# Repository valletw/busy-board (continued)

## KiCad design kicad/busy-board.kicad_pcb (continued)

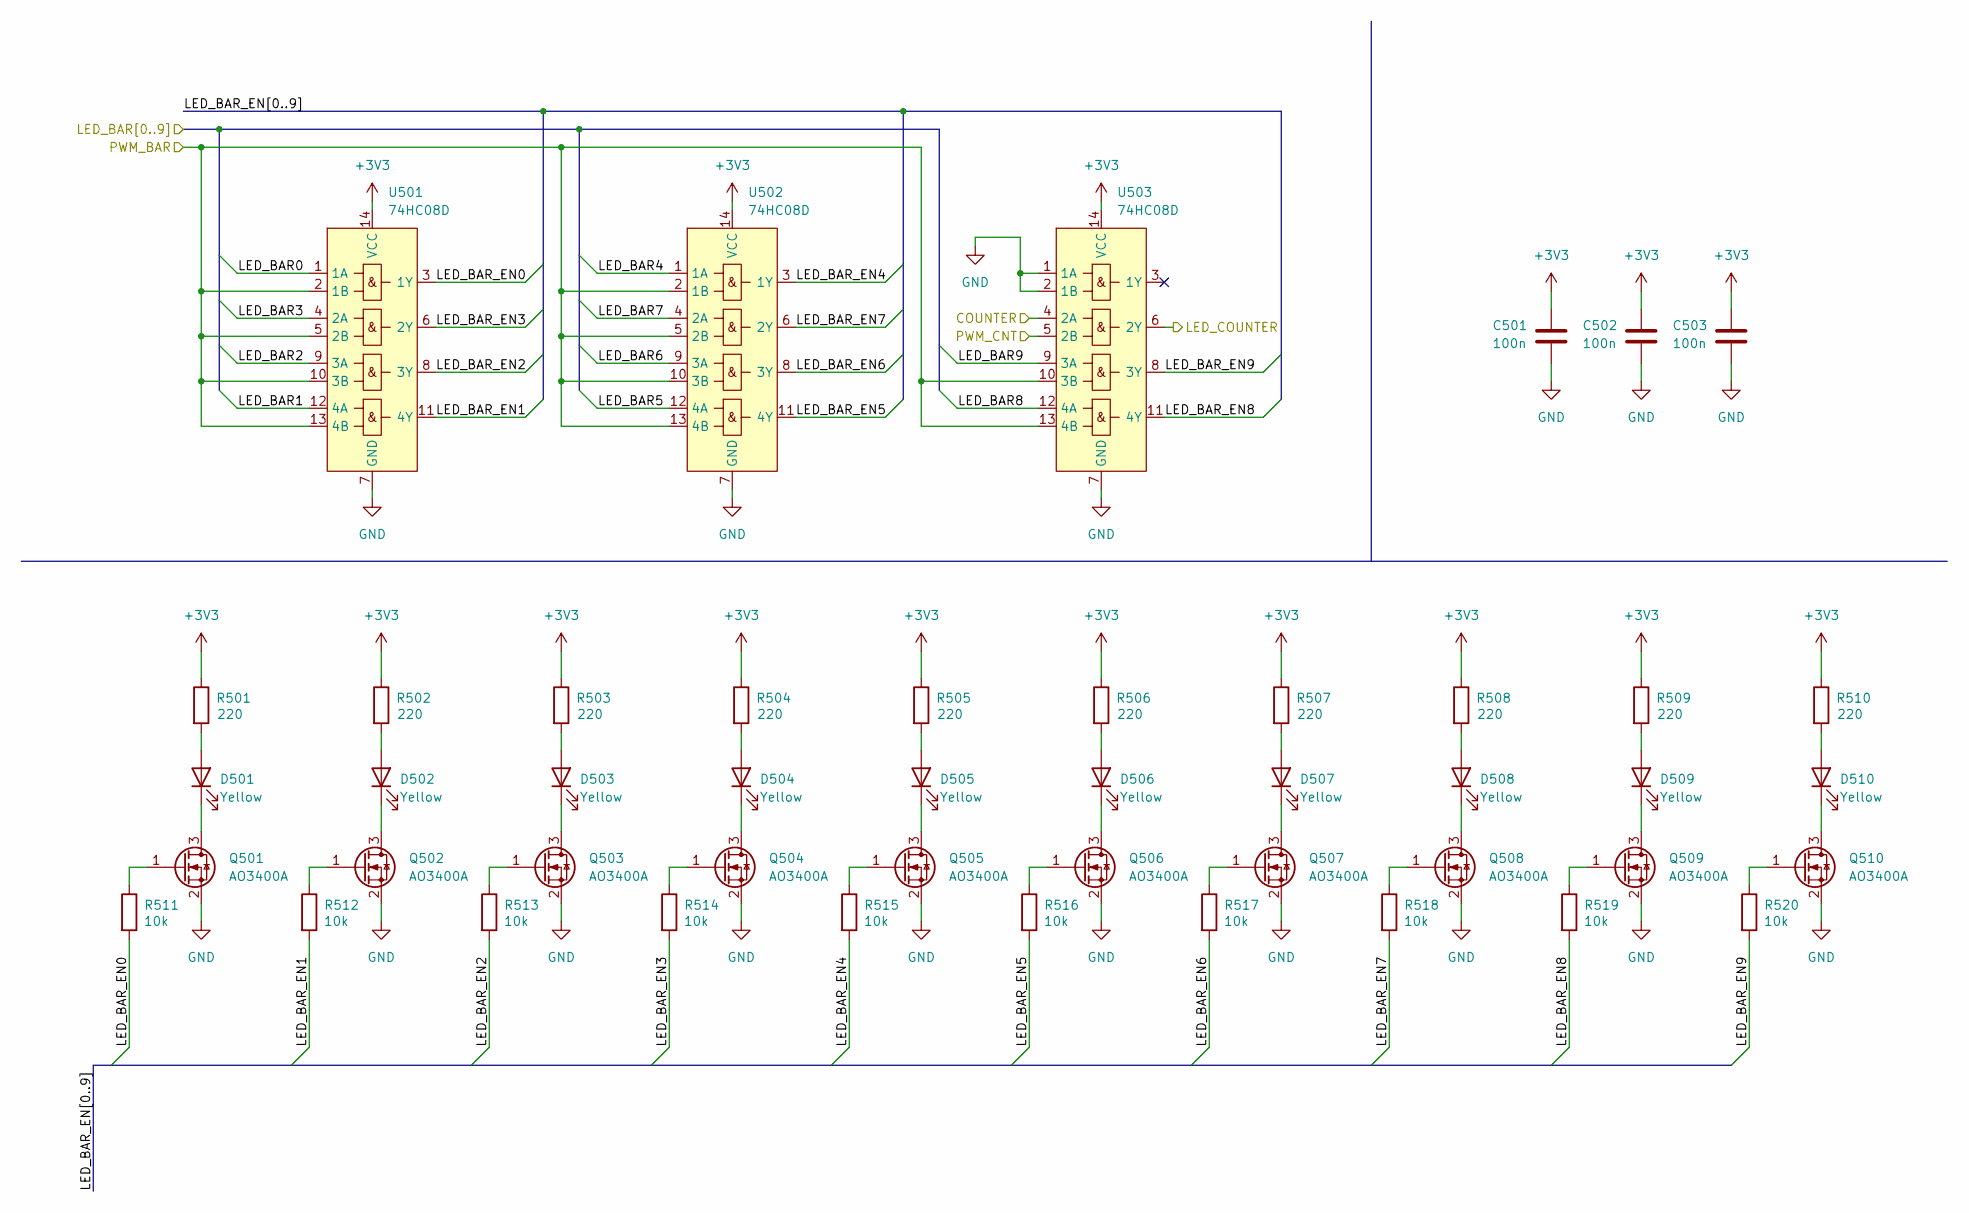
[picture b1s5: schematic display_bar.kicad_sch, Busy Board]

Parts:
C501, C502, C503: 100n; C_0402_1005Metric; MFR Part # CL05B104KB54PNC; LCSC Part # C307331
D501, D502, D503, D504, D505, D506, D507, D508, D509, D510: Yellow; LED_0805_2012Metric; MFR Part # KT-0805Y; LCSC Part # C2296
Q501, Q502, Q503, Q504, Q505, Q506, Q507, Q508, Q509, Q510: AO3400A; SOT-23; MFR Part # AO3400A; LCSC Part # C20917
R501, R502, R503, R504, R505, R506, R507, R508, R509, R510: 220; R_0603_1608Metric; MFR Part # 0603WAF2200T5E; LCSC Part # C22962
R511, R512, R513, R514, R515, R516, R517, R518, R519, R520: 10k; R_0603_1608Metric; MFR Part # 0603WAF1002T5E; LCSC Part # C25804
U501, U502, U503: 74HC08D; SOIC-14_3.9x8.7mm_P1.27mm; MFR Part # 74HC08D,653; LCSC Part # C5593

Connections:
+3V3: C501.1, C502.1, C503.1, R501.1, R502.1, R503.1, R504.1, R505.1, R506.1, R507.1, R508.1, R509.1, R510.1, U501.14 (VCC), U502.14 (VCC), U503.14 (VCC); also elsewhere on the board
/CLK_CNT: U503.4 (2A); also elsewhere on the board
/Counter/Display Bar/LED_BAR_EN0: R511.2, U501.3 (1Y)
/Counter/Display Bar/LED_BAR_EN1: R512.2, U501.11 (4Y)
/Counter/Display Bar/LED_BAR_EN2: R513.2, U501.8 (3Y)
/Counter/Display Bar/LED_BAR_EN3: R514.2, U501.6 (2Y)
/Counter/Display Bar/LED_BAR_EN4: R515.2, U502.3 (1Y)
/Counter/Display Bar/LED_BAR_EN5: R516.2, U502.11 (4Y)
/Counter/Display Bar/LED_BAR_EN6: R517.2, U502.8 (3Y)
/Counter/Display Bar/LED_BAR_EN7: R518.2, U502.6 (2Y)
/Counter/Display Bar/LED_BAR_EN8: R519.2, U503.11 (4Y)
/Counter/Display Bar/LED_BAR_EN9: R520.2, U503.8 (3Y)
/Counter/LED_BAR0: U501.1 (1A); also elsewhere on the board
/Counter/LED_BAR1: U501.12 (4A); also elsewhere on the board
/Counter/LED_BAR2: U501.9 (3A); also elsewhere on the board
/Counter/LED_BAR3: U501.4 (2A); also elsewhere on the board
/Counter/LED_BAR4: U502.1 (1A); also elsewhere on the board
/Counter/LED_BAR5: U502.12 (4A); also elsewhere on the board
/Counter/LED_BAR6: U502.9 (3A); also elsewhere on the board
/Counter/LED_BAR7: U502.4 (2A); also elsewhere on the board
/Counter/LED_BAR8: U503.12 (4A); also elsewhere on the board
/Counter/LED_BAR9: U503.9 (3A); also elsewhere on the board
/Counter/LED_COUNTER: U503.6 (2Y); also elsewhere on the board
/Counter/PWM_LED_BAR: U501.2 (1B), U501.5 (2B), U501.10 (3B), U501.13 (4B), U502.2 (1B), U502.5 (2B), U502.10 (3B), U502.13 (4B), U503.10 (3B), U503.13 (4B); also elsewhere on the board
/Counter/PWM_LED_COUNTER: U503.5 (2B); also elsewhere on the board
GND: C501.2, C502.2, C503.2, Q501.2 (S), Q502.2 (S), Q503.2 (S), Q504.2 (S), Q505.2 (S), Q506.2 (S), Q507.2 (S), Q508.2 (S), Q509.2 (S), Q510.2 (S), U501.7 (GND), U502.7 (GND), U503.1 (1A), U503.2 (1B), U503.7 (GND); also elsewhere on the board
unnamed: D501.2 (A), R501.2
unnamed: D501.1 (K), Q501.3 (D)
unnamed: D502.2 (A), R502.2
unnamed: D502.1 (K), Q502.3 (D)
unnamed: D503.2 (A), R503.2
unnamed: D503.1 (K), Q503.3 (D)
unnamed: D504.2 (A), R504.2
unnamed: D504.1 (K), Q504.3 (D)
unnamed: D505.2 (A), R505.2
unnamed: D505.1 (K), Q505.3 (D)
unnamed: D506.2 (A), R506.2
unnamed: D506.1 (K), Q506.3 (D)
unnamed: D507.2 (A), R507.2
unnamed: D507.1 (K), Q507.3 (D)
unnamed: D508.2 (A), R508.2
unnamed: D508.1 (K), Q508.3 (D)
unnamed: D509.2 (A), R509.2
unnamed: D509.1 (K), Q509.3 (D)
unnamed: D510.2 (A), R510.2
unnamed: D510.1 (K), Q510.3 (D)
unnamed: Q501.1 (G), R511.1
unnamed: Q502.1 (G), R512.1
unnamed: Q503.1 (G), R513.1
unnamed: Q504.1 (G), R514.1
unnamed: Q505.1 (G), R515.1
unnamed: Q506.1 (G), R516.1
unnamed: Q507.1 (G), R517.1
unnamed: Q508.1 (G), R518.1
unnamed: Q509.1 (G), R519.1
unnamed: Q510.1 (G), R520.1

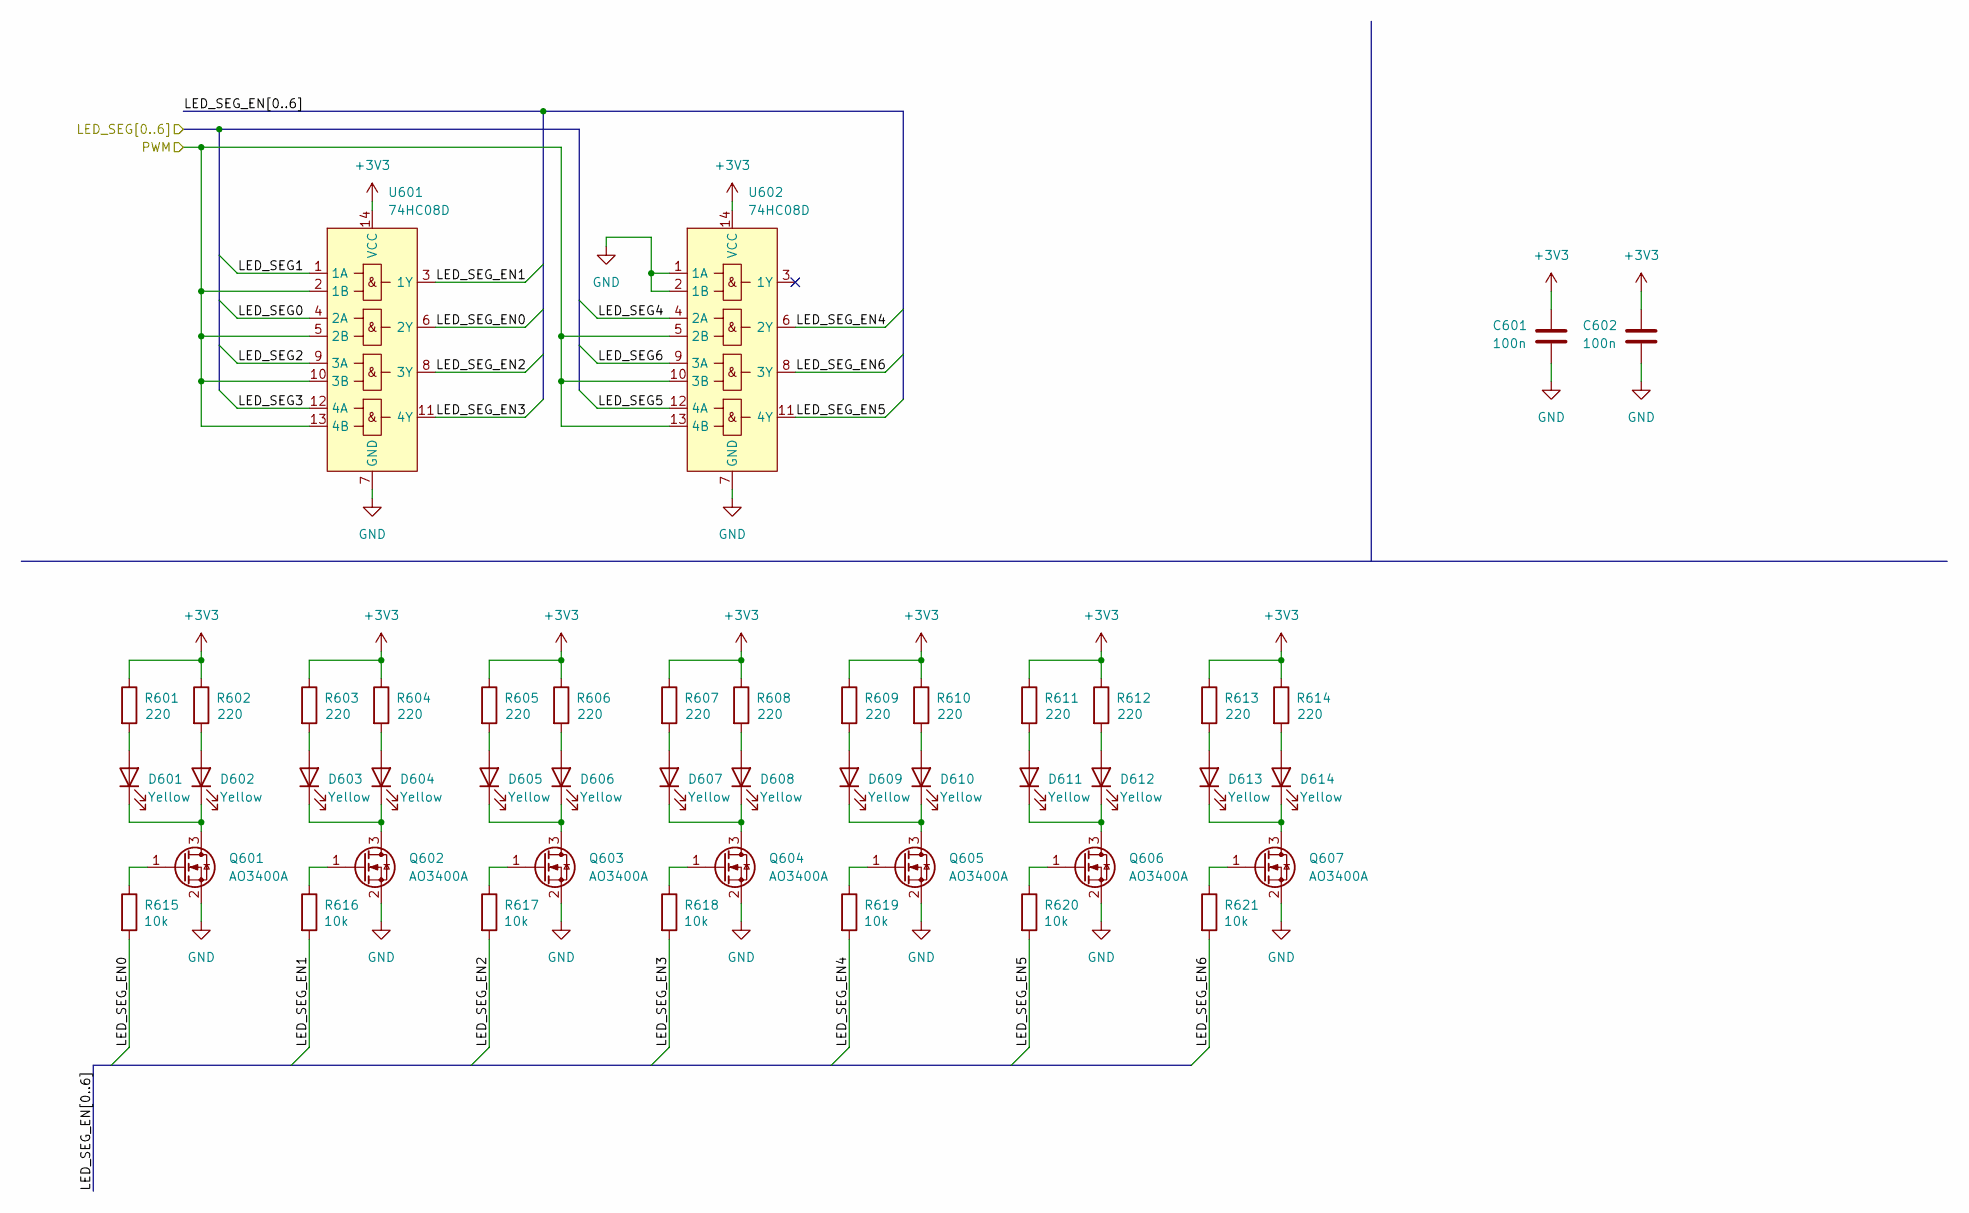
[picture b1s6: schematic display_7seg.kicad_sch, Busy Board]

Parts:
C601, C602: 100n; C_0402_1005Metric; MFR Part # CL05B104KB54PNC; LCSC Part # C307331
D601, D602, D603, D604, D605, D606, D607, D608, D609, D610, D611, D612, D613, D614: Yellow; LED_0805_2012Metric; MFR Part # KT-0805Y; LCSC Part # C2296
Q601, Q602, Q603, Q604, Q605, Q606, Q607: AO3400A; SOT-23; MFR Part # AO3400A; LCSC Part # C20917
R601, R602, R603, R604, R605, R606, R607, R608, R609, R610, R611, R612, R613, R614: 220; R_0603_1608Metric; MFR Part # 0603WAF2200T5E; LCSC Part # C22962
R615, R616, R617, R618, R619, R620, R621: 10k; R_0603_1608Metric; MFR Part # 0603WAF1002T5E; LCSC Part # C25804
U601, U602: 74HC08D; SOIC-14_3.9x8.7mm_P1.27mm; MFR Part # 74HC08D,653; LCSC Part # C5593

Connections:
+3V3: C601.1, C602.1, R601.1, R602.1, R603.1, R604.1, R605.1, R606.1, R607.1, R608.1, R609.1, R610.1, R611.1, R612.1, R613.1, R614.1, U601.14 (VCC), U602.14 (VCC); also elsewhere on the board
/Counter/Display 7 Segments/LED_SEG_EN0: R615.2, U601.6 (2Y)
/Counter/Display 7 Segments/LED_SEG_EN1: R616.2, U601.3 (1Y)
/Counter/Display 7 Segments/LED_SEG_EN2: R617.2, U601.8 (3Y)
/Counter/Display 7 Segments/LED_SEG_EN3: R618.2, U601.11 (4Y)
/Counter/Display 7 Segments/LED_SEG_EN4: R619.2, U602.6 (2Y)
/Counter/Display 7 Segments/LED_SEG_EN5: R620.2, U602.11 (4Y)
/Counter/Display 7 Segments/LED_SEG_EN6: R621.2, U602.8 (3Y)
/Counter/LED_SEG0: U601.4 (2A); also elsewhere on the board
/Counter/LED_SEG1: U601.1 (1A); also elsewhere on the board
/Counter/LED_SEG2: U601.9 (3A); also elsewhere on the board
/Counter/LED_SEG3: U601.12 (4A); also elsewhere on the board
/Counter/LED_SEG4: U602.4 (2A); also elsewhere on the board
/Counter/LED_SEG5: U602.12 (4A); also elsewhere on the board
/Counter/LED_SEG6: U602.9 (3A); also elsewhere on the board
/Counter/PWM_LED_SEG: U601.2 (1B), U601.5 (2B), U601.10 (3B), U601.13 (4B), U602.5 (2B), U602.10 (3B), U602.13 (4B); also elsewhere on the board
GND: C601.2, C602.2, Q601.2 (S), Q602.2 (S), Q603.2 (S), Q604.2 (S), Q605.2 (S), Q606.2 (S), Q607.2 (S), U601.7 (GND), U602.1 (1A), U602.2 (1B), U602.7 (GND); also elsewhere on the board
unnamed: D601.2 (A), R601.2
unnamed: D601.1 (K), D602.1 (K), Q601.3 (D)
unnamed: D602.2 (A), R602.2
unnamed: D603.2 (A), R603.2
unnamed: D603.1 (K), D604.1 (K), Q602.3 (D)
unnamed: D604.2 (A), R604.2
unnamed: D605.2 (A), R605.2
unnamed: D605.1 (K), D606.1 (K), Q603.3 (D)
unnamed: D606.2 (A), R606.2
unnamed: D607.2 (A), R607.2
unnamed: D607.1 (K), D608.1 (K), Q604.3 (D)
unnamed: D608.2 (A), R608.2
unnamed: D609.2 (A), R609.2
unnamed: D609.1 (K), D610.1 (K), Q605.3 (D)
unnamed: D610.2 (A), R610.2
unnamed: D611.2 (A), R611.2
unnamed: D611.1 (K), D612.1 (K), Q606.3 (D)
unnamed: D612.2 (A), R612.2
unnamed: D613.2 (A), R613.2
unnamed: D613.1 (K), D614.1 (K), Q607.3 (D)
unnamed: D614.2 (A), R614.2
unnamed: Q601.1 (G), R615.1
unnamed: Q602.1 (G), R616.1
unnamed: Q603.1 (G), R617.1
unnamed: Q604.1 (G), R618.1
unnamed: Q605.1 (G), R619.1
unnamed: Q606.1 (G), R620.1
unnamed: Q607.1 (G), R621.1

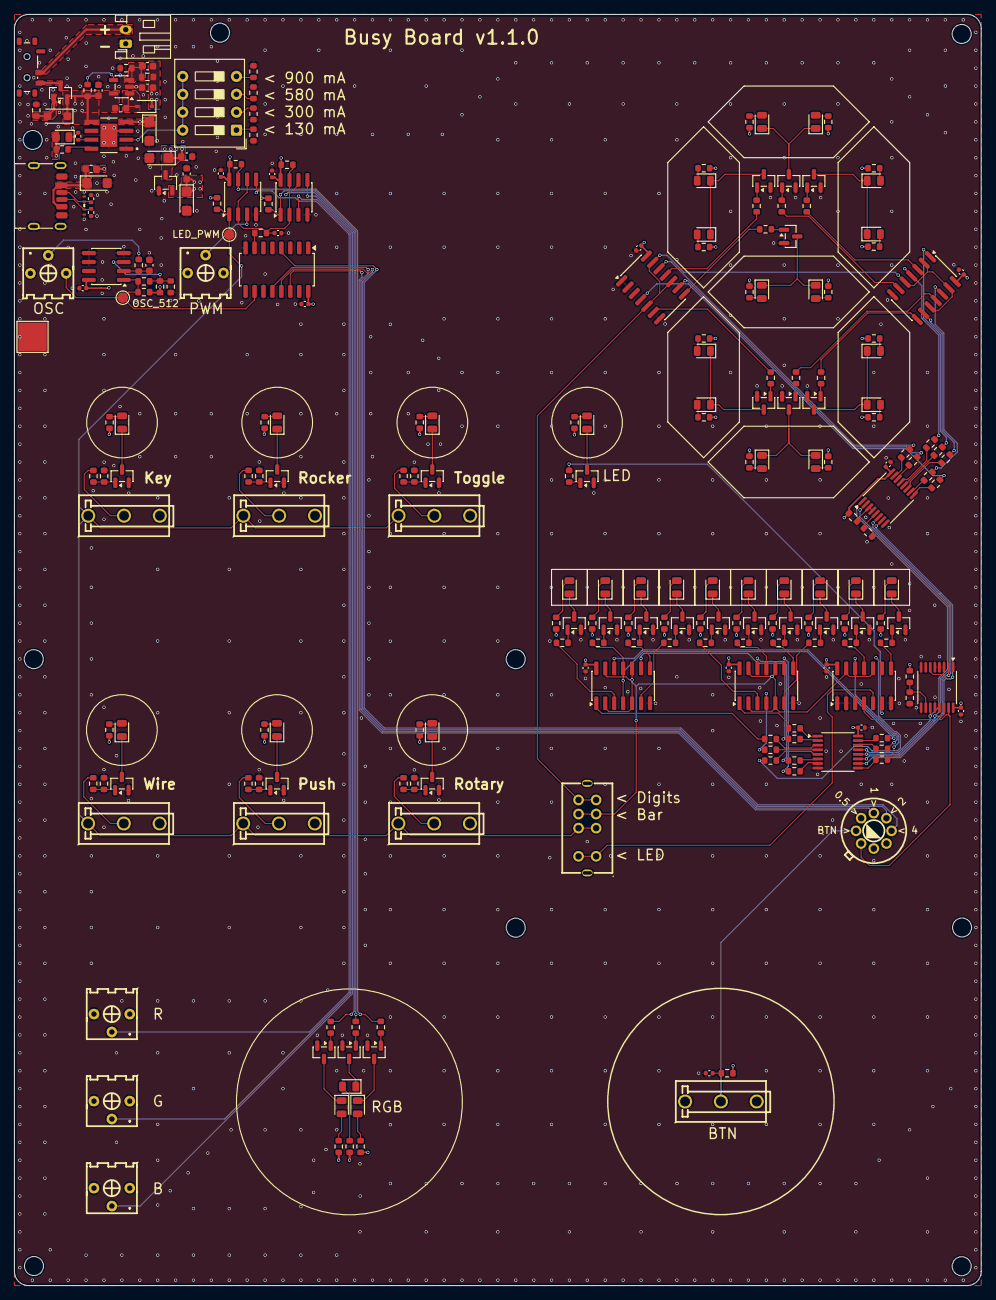
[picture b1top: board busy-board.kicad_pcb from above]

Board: 4 copper layers, 137.2 x 180.3 mm, 249 parts (0 on the bottom side), 198 nets.

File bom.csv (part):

"Reference","Value","Qty","Footprint","Manufacturer","MFR Part #","LCSC Part #","Datasheet"
"C101,C202,C204","100n","3","Capacitor_SMD:C_0603_1608Metric","YAGEO","CC0603JRX7R7BB104,CC0603KRX7R9BB104","C14663,C91183","https://jlcpcb.com/api/file/downloadByFileSystemAccessId/866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,https://www.lcsc.com/datasheet/C91183.pdf"
"C102,C103,C104,C105,C106,C107,C401,C402,C403,C501,C502,C503,C601,C602","100n","14","Capacitor_SMD:C_0402_1005Metric","Samsung Electro-Mechanics","CL05B104KB54PNC","C307331","https://jlcpcb.com/api/file/downloadByFileSystemAccessId/855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"
"C201,C203,C208","10u","3","Capacitor_Tantalum_SMD:CP_EIA-3216-18_Kemet-A","-","TAJA106K016RNJ","C7171","~"
"C205","22p","1","Capacitor_SMD:C_0603_1608Metric","Samsung Electro-Mechanics","CL10C220JB8NNNC","C1653","https://jlcpcb.com/api/file/downloadByFileSystemAccessId/866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"
"C206","1u","1","Capacitor_SMD:C_0603_1608Metric","Samsung Electro-Mechanics","CL10A105KB8NNNC","C15849","https://jlcpcb.com/api/file/downloadByFileSystemAccessId/866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"
"C207","4.7u","1","Capacitor_SMD:C_0603_1608Metric","Samsung Electro-Mechanics","CL10A475KO8NNNC","C19666","https://jlcpcb.com/api/file/downloadByFileSystemAccessId/866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 0 0 Centrer Centrer 0 0"
"D201","BZT52Bxx","1","Diode_SMD:D_SOD-123F","hongjiacheng","BZT52B5V1","C19077393","https://diotec.com/tl_files/diotec/files/pdf/datasheets/bzt5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"
"D202","SMF5V0A","1","Diode_SMD:D_SMF","hongjiacheng","SMF5.0A","C19077497","https://www.vishay.com/doc?85881"
"D203","B0540WS","1","Diode_SMD:D_SOD-323","hongjiacheng","B0540WS","C7420326","https://jlc-prod-smt.oss-eu-central-1.aliyuncs.com/smtDataMa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"
"D204,D301,D304","Red","3","LED_SMD:LED_0805_2012Metric","Foshan NationStar Optoelectronics","NCD0805R1","C84256","https://jlcpcb.com/api/file/downloadByFileSystemAccessId/855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,https://www.lcsc.com/datasheet/C84256.pdf"
"D302,D306","Green","2","LED_SMD:LED_0805_2012Metric","Hubei KENTO Elec","KT-0805G","C2297","https://www.lcsc.com/datasheet/C2297.pdf"
"D303,D308","Blue","2","LED_SMD:LED_0805_2012Metric","Foshan NationStar Optoelectronics","NCD0805B2","C84259","https://www.lcsc.com/datasheet/C84259.pdf"
"D305","Orange","1","LED_SMD:LED_0805_2012Metric","Foshan NationStar Optoelectronics","NCD0805O1","C84262","https://www.lcsc.com/datasheet/C84262.pdf"
"D307","White","1","LED_SMD:LED_0805_2012Metric","Hubei KENTO Elec","KT-0805W","C34499","https://www.lcsc.com/datasheet/C34499.pdf"
"D309","Purple","1","LED_SMD:LED_0805_2012Metric","XINGLIGHT","XL-2012UVA","C7371915","https://www.lcsc.com/datasheet/C7371915.pdf"
"D401,D501,D502,D503,D504,D505,D506,D507,D508,D509,D510,D601,D602,D603,D604,D605,D606,D607,D608,D609,D610,D611,D612,D613,D614","Yellow","25","LED_SMD:LED_0805_2012Metric","Hubei KENTO Elec","KT-0805Y","C2296","https://www.lcsc.com/datasheet/C2296.pdf"
"H101,H102,H103,H104,H105,H106,H107,H108,H109","MountingHole","9","MountingHole:MountingHole_2.7mm_M2.5_ISO7380","","","","~"
"J201","JST PH 2P","1","Connector_JST:JST_PH_S2B-PH-K_1x02_P2.00mm_Horizontal","JST","S2B-PH-K-S(LF)(SN)","C173752","https://jlcpcb.com/api/file/downloadByFileSystemAccessId/858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"
"J202","USB_C_Receptacle_PowerOnly_6P","1","Connector_USB:USB_C_Receptacle_HRO_TYPE-C-31-M-17","Korean Hroparts Elec","TYPE-C-31-M-17","C283540","https://jlcpcb.com/api/file/downloadByFileSystemAccessId/858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"
"L201","Ferrite Bead","1","Inductor_SMD:L_0603_1608Metric","Murata Electronics","BLM18PG121SN1D","C14709","https://pim.murata.com/en-eu/pim/details/?productCategoryId=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"
"L202","10u","1","Inductor_SMD:L_0603_1608Metric","Sunlord","SDFL1608S100KTF","C1035","https://jlc-prod-smt.oss-eu-central-1.aliyuncs.com/smtDataMa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"
"Q201","AO3401A","1","Package_TO_SOT_SMD:SOT-23","Alpha & Omega Semicon","AO3401A","C15127","https://jlcpcb.com/api/file/downloadByFileSystemAccessId/855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"
"Q301,Q302,Q303,Q304,Q305,Q306,Q307,Q308,Q309,Q401,Q501,Q502,Q503,Q504,Q505,Q506,Q507,Q508,Q509,Q510,Q601,Q602,Q603,Q604,Q605,Q606,Q607","MMBT3904","27","Package_TO_SOT_SMD:SOT-23","hongjiacheng","MMBT3904","C7420353","https://jlcpcb.com/api/file/downloadByFileSystemAccessId/856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"
"R101,R102,R103,R104,R105,R107,R108,R109,R110,R111,R209,R304,R305,R306,R311,R312,R313,R314,R321,R322,R408,R414,R418,R422,R511,R512,R513,R514,R515,R516,R517,R518,R519,R520,R615,R616,R617,R618,R619,R620,R621","10k","41","Resistor_SMD:R_0603_1608Metric","UNI-ROYAL(Uniroyal Elec)","0603WAF1002T5E","C25804","https://jlcpcb.com/api/file/downloadByFileSystemAccessId/857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,https://jlcpcb.com/api/file/downloadByFileSystemAccessId/857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"
"R106","9.1k","1","Resistor_SMD:R_0603_1608Metric","UNI-ROYAL(Uniroyal Elec)","0603WAF9101T5E","C23260","https://jlcpcb.com/api/file/downloadByFileSystemAccessId/857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"
"R201,R315,R316,R317,R318,R323,R324","100k","7","Resistor_SMD:R_0603_1608Metric","UNI-ROYAL(Uniroyal Elec)","0603WAF1003T5E","C25803","https://jlcpcb.com/api/file/downloadByFileSystemAccessId/857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"
"R202","680k","1","Resistor_SMD:R_0603_1608Metric","UNI-ROYAL(Uniroyal Elec)","0603WAF6803T5E","C25822","https://jlcpcb.com/api/file/downloadByFileSystemAccessId/857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"
"R203,R207","0","2","Resistor_SMD:R_0603_1608Metric","UNI-ROYAL(Uniroyal Elec)","0603WAF0000T5E","C21189","https://jlcpcb.com/api/file/downloadByFileSystemAccessId/857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"
"R204,R205","5.1k","2","Resistor_SMD:R_0402_1005Metric","UNI-ROYAL(Uniroyal Elec)","0402WGF5101TCE","C25905","https://jlcpcb.com/api/file/downloadByFileSystemAccessId/857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"
"R206","220k","1","Resistor_SMD:R_0603_1608Metric","UNI-ROYAL(Uniroyal Elec)","0603WAF2203T5E","C22961","https://jlcpcb.com/api/file/downloadByFileSystemAccessId/857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"
"R208","220","1","Resistor_SMD:R_0402_1005Metric","UNI-ROYAL(Uniroyal Elec)","0402WGF5101TCE","C25905","https://jlcpcb.com/api/file/downloadByFileSystemAccessId/857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"
"R210","3.9k","1","Resistor_SMD:R_0603_1608Metric","UNI-ROYAL(Uniroyal Elec)","0603WAF3901T5E","C23018","https://jlcpcb.com/api/file/downloadByFileSystemAccessId/857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"
"R211","2k","1","Resistor_SMD:R_0603_1608Metric","UNI-ROYAL(Uniroyal Elec)","0603WAF2001T5E","C22975","https://jlcpcb.com/api/file/downloadByFileSystemAccessId/857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"
"R212","1.2k","1","Resistor_SMD:R_0603_1608Metric","UNI-ROYAL(Uniroyal Elec)","0603WAF1201T5E","C22765","https://jlcpcb.com/api/file/downloadByFileSystemAccessId/857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"
"R301,R307","270","2","Resistor_SMD:R_0603_1608Metric","UNI-ROYAL(Uniroyal Elec)","0603WAF2700T5E","C22966","https://jlcpcb.com/api/file/downloadByFileSystemAccessId/857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"
"R302,R303,R309,R310,R319","390","5","Resistor_SMD:R_0603_1608Metric","UNI-ROYAL(Uniroyal Elec)","0603WAF3900T5E","C23151","https://jlcpcb.com/api/file/downloadByFileSystemAccessId/857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"
"R308,R413,R501,R502,R503,R504,R505,R506,R507,R508,R509,R510,R601,R602,R603,R604,R605,R606,R607,R608,R609,R610,R611,R612,R613,R614","220","26","Resistor_SMD:R_0603_1608Metric","UNI-ROYAL(Uniroyal Elec)","0603WAF2200T5E","C22962","https://jlcpcb.com/api/file/downloadByFileSystemAccessId/857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"
"R320","360","1","Resistor_SMD:R_0603_1608Metric","UNI-ROYAL(Uniroyal Elec)","0603WAF3600T5E","C25194","https://jlcpcb.com/api/file/downloadByFileSystemAccessId/857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"
"R401,R402,R403,R404,R405,R406,R407,R409,R411,R412,R415,R416,R417,R419,R420,R421,R423","1k","17","Resistor_SMD:R_0603_1608Metric","UNI-ROYAL(Uniroyal Elec)","0603WAF1001T5E","C21190","https://jlcpcb.com/api/file/downloadByFileSystemAccessId/857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"
"RV101,RV102,RV103,RV104,RV105","3362P","5","footprints:BOURNS_3362P","BOURNS","3362P-1-103LF","C58159","https://www.lcsc.com/datasheet/C58159.pdf"
"SW101","MAN_CNT","1","footprints:SW-TH_DM1-12UP-1","XKB Connection","DM1-12UP-1","C405949","https://www.lcsc.com/datasheet/C405949.pdf"
"SW102","CLK_SELECT","1","footprints:SW-TH_RT-0C4-D","Dailywell","RT-0C5","C508440","https://www.lcsc.com/datasheet/C508440.pdf"
"SW201","SW_DIP_x04","1","Button_Switch_THT:SW_DIP_SPSTx04_Slide_9.78x12.34mm_W7.62mm_P2.54mm","DongGuan KINGTEK Industrial Co.,LTD","DSWB04LHGET","C99418","https://jlc-prod-smt.oss-eu-central-1.aliyuncs.com/smtDataMa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"
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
